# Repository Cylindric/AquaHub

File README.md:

# AquaHub

# Key Components

## Hardware

The electronic designs are all made using [KiCad](http://kicad-pcb.org).

The actual KiCad project files are [here](Hardware/AquaHub/).

Rendered output (schematic and board PDFs, gerbers and bom) are [here](Hardware/Output/). (Not always up-to-date with the schematics and boards, so use with caution)

### License

All hardware designs are licensed under the [CERN Open Hardware Licence v1.2](https://www.ohwr.org/licenses/cern-ohl/license_versions/v1.2).

Myriam Ayass, legal adviser of the Knowledge and Technology Transfer Group at CERN and author of the CERN OHL:

> In the spirit of knowledge sharing and dissemination, the CERN Open Hardware Licence (CERN OHL) governs the use, copying, modification and distribution of hardware design documentation, and the manufacture and distribution of products.
> 
> The CERN–OHL is to hardware what the General Public Licence (GPL) is to software. It defines the conditions under which a licensee will be able to use or modify the licensed material. The concept of ‘open-source hardware’ or ‘open hardware’ is not yet as well known or widespread as the free software or open-source software concept. However, it shares the same principles: anyone should be able to see the source (the design documentation in case of hardware), study it, modify it and share it.
> 
> In addition, if modifications are made and distributed, it must be under the same licence conditions – this is the ‘persistent’ nature of the licence, which ensures that the whole community will continue benefiting from improvements, in the sense that everyone will in turn be able to make modifications to these improvements.

### Rev 1
- [x] ESP32 module for control and wireless access (Espressif ESP32-WROOM-32D)
- [x] Current Sensing for consumption reporting and equipment failure detection (Melexis MLX91210KDC)
- [x] RTC for power-loss schedule persistence (Maxim DS1307Z)
- [x] Temperature monitoring (DS18B20)
- [x] Audible alarm
- [x] Six switchable mains-level outputs (Fujitsu FTR-F1A)
- [x] Direct mains-powered (Recom RAC04-12SGB)

### Rev 2
- [ ] PCB: selectable low-level power select, for testing from a 12V supply instead of 240V
- [x] PCB: additional sensor for ambient temperature (on-board or external?)
- [ ] PCB: additional input for flow-rate sensor
- [ ] PCB: additional input for pH sensor (might not be feasible without a permanent-immersion sensor?)
- [ ] PCB: LED power indication for ESP
- [x] PCB: Reset button for ESP
- [x] PCB: Test points for probe hooks
- [x] PCB: Change buttons to off-board panel buttons
- [ ] ENCLOSURE: Add a 6-pin socket for programming
- [ ] ENCLOSURE: Switched & fused power inlet receptacle
- [ ] ENCLOSURE: Non-PCB panel buttons - more choice, better buttons
- [ ] ENCLOSURE: Power LED

## Software

### License

All software (firmware) are Copyright 2018 Mark Hanford and licensed under the [Apache License, Version 2.0](http://www.apache.org/licenses/LICENSE-2.0) (the "License");

> You may not use this file except in compliance with the License. You may obtain a copy of the License at
>
> http://www.apache.org/licenses/LICENSE-2.0
>
> Unless required by applicable law or agreed to in writing, software distributed under the License is distributed on an "AS IS" BASIS, WITHOUT WARRANTIES OR CONDITIONS OF ANY KIND, either express or implied.
> See the License for the specific language governing permissions and limitations under the License.

### Rev 1
- [ ] Over-the-air firmware updates
- [ ] Web UI
- [ ] Task Scheduler
- [ ] Temperature-based control
- [ ] Temperature alarm
- [ ] Pump-fail alarm
- [ ] WiFi config

# Hardware Build

A Mouser project with some of the components listed in detail is available here: [AquaHub At Mouser](https://www.mouser.com/ProjectManager/ProjectDetail.aspx?AccessID=329311b4a5). Not always updated with the current BOM from the schematic, and parts change so may be unavailable. CHECK THE SCHEMATIC.

## Datasheets

* [Espressif ESP32 WROOM 32D](https://www.espressif.com/sites/default/files/documentation/esp32-wroom-32d_esp32-wroom-32u_datasheet_en.pdf)
* [Recom 5v Regulator](https://www.recom-power.com/pdf/Innoline/R-78Exx-0.5.pdf)
* [Diodes 3.3V Regulator](http://www.diodes.com/datasheets/AP1117.pdf)
* [2SC1815 Transistor](https://media.digikey.com/pdf/Data%20Sheets/Toshiba%20PDFs/2SC1815.pdf)
* [Maxim I²C RTC](https://datasheets.maximintegrated.com/en/ds/DS1307.pdf)
* [TI I²C IO Expander](http://www.ti.com/lit/ds/symlink/tca9534.pdf)
* [TI I²C LED Driver](http://www.ti.com/lit/ds/symlink/tpic2810.pdf)

## References

* DS18B20 temperature - [ESP32 With Multiple DS18B20 Sensors](https://randomnerdtutorials.com/esp32-with-multiple-ds18b20-temperature-sensors/)

# Attribution

* Fish icon is from [iconsDB](https://www.iconsdb.com/custom-color/fish-3-icon.html); Creative Commons Attribution-NoDerivs 3.0.

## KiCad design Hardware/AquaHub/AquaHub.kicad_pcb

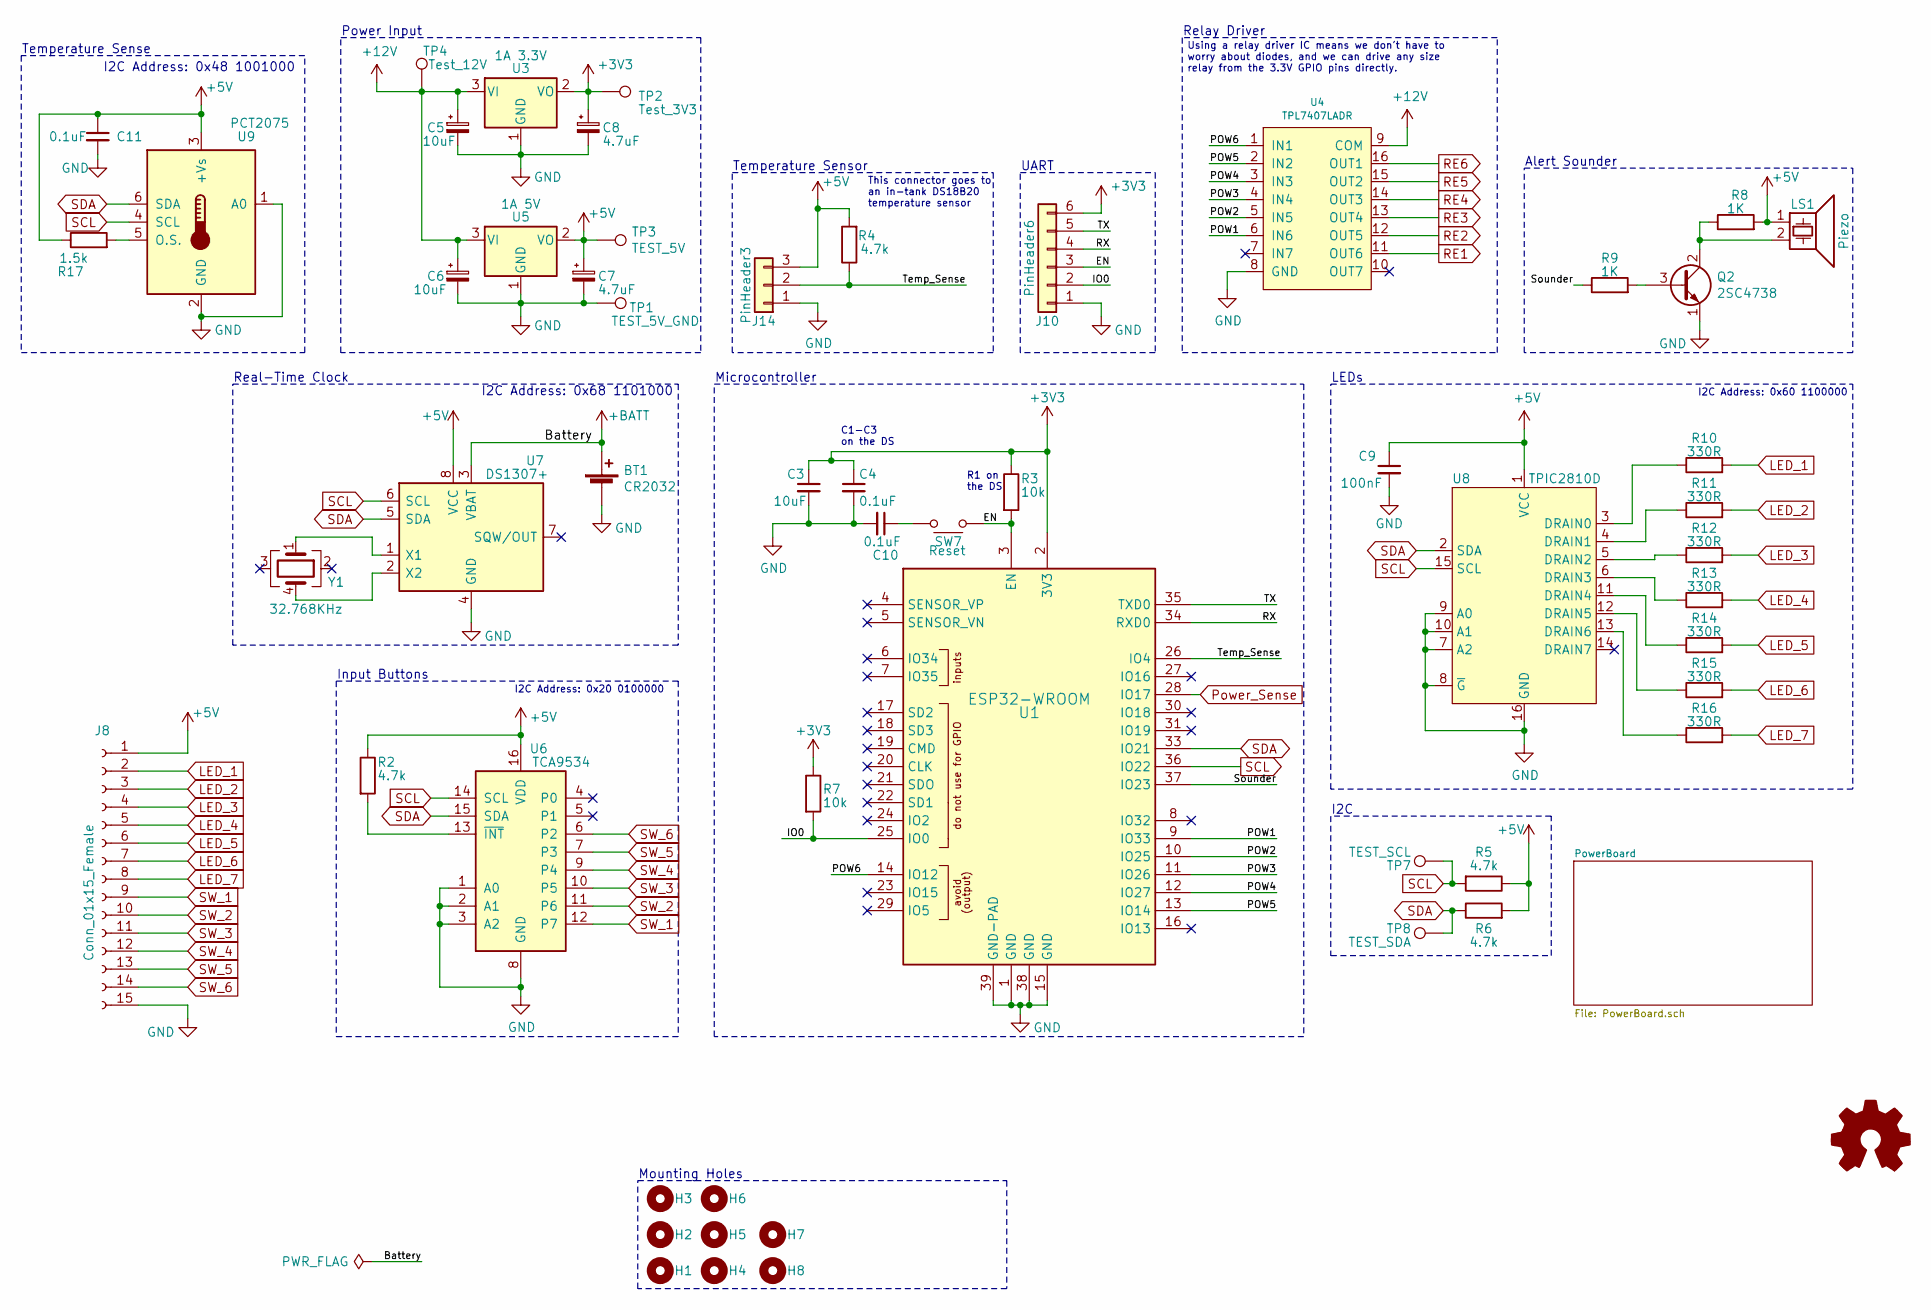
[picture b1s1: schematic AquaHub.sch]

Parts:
BT1: CR2032; BatteryHolder_Multicomp_BC-2001_1x2032; Mouser 534-1058
C3: 10uF; C_0805_2012Metric_Pad1.15x1.40mm_HandSolder; Mouser TAJB106K006SNJ
C4, C10, C11: 0.1uF; C_0805_2012Metric_Pad1.15x1.40mm_HandSolder; Mouser TAJB106K006SNJ
C5, C6: 10uF; CP_Elec_6.3x5.4_Nichicon; Farnell CA07886
C7, C8: 4.7uF; CP_Elec_5x5.4; Mouser UWX1H4R7MCL1GB
C9: 100nF; C_0603_1608Metric_Pad1.05x0.95mm_HandSolder; Farnell CA07658
H1, H2, H3, H4, H5, H6, H7, H8: MountingHole; MountingHole_3.2mm_M3
J8: Conn_01x15_Female; PinHeader_2x08_P2.00mm_Vertical; Mouser 798-DF51A-16DP-2DSA
J10: PinHeader6; PinHeader_1x06_P2.54mm_Vertical; Mouser 710-61300611121
J14: PinHeader3; PinHeader_1x03_P2.54mm_Vertical; Mouser 710-61300311121
LS1: Piezo; Buzzer_TDK_PS1240P02BT_D12.2mm_H6.5mm; Mouser PS1240P02BT
Q2: 2SC4738; SOT-416; Farnell SC06581
R2, R4, R5, R6: 4.7k; R_0603_1608Metric_Pad1.05x0.95mm_HandSolder; Mouser 603-RC0603FR-074K7L
R3, R7: 10k; R_0603_1608Metric_Pad1.05x0.95mm_HandSolder; Mouser 603-RC0603FR-0710KL
R8, R9: 1K; R_0603_1608Metric_Pad1.05x0.95mm_HandSolder; Farnell RE07090
R10, R11, R12, R13, R14, R15, R16: 330R; R_0603_1608Metric_Pad1.05x0.95mm_HandSolder; Farnell RE07105
R17: 1.5k; R_0603_1608Metric_Pad1.05x0.95mm_HandSolder; Mouser 603-RC0603FR-101K5L
SW7: Reset; SW_SPST_PTS645; Mouser 611-PTS645SM43SMTR92
TP1: TEST_5V_GND; TestPoint_Loop_D2.50mm_Drill1.0mm
TP2: Test_3V3; TestPoint_Loop_D2.50mm_Drill1.0mm
TP3: TEST_5V; TestPoint_Loop_D2.50mm_Drill1.0mm
TP4: Test_12V; TestPoint_Loop_D2.50mm_Drill1.0mm
TP7: TEST_SCL; TestPoint_Loop_D2.50mm_Drill1.0mm
TP8: TEST_SDA; TestPoint_Loop_D2.50mm_Drill1.0mm
U1: ESP32-WROOM; Espressif_ESP32_WROOM_32_SMT; Mouser ESP32-WROOM-32D
U3: 1A 3.3V; TO-252-3_TabPin2; Mouser NCP1117DT33G
U4: TPL7407LADR; SOIC-16_3.9x9.9mm_P1.27mm; Mouser 595-TPL7407LADR
U5: 1A 5V; TO-252-3_TabPin2; Mouser NCP1117DT50G
U6: TCA9534; SOIC-16W_7.5x10.3mm_P1.27mm; Mouser TCA9534DWR
U7: DS1307+; SOIC-8_3.9x4.9mm_P1.27mm; Mouser 700-DS1307ZT&R
U8: TPIC2810D; SOIC-16_3.9x9.9mm_P1.27mm; Mouser 595-TPIC2810DR
U9: PCT2075; TSOP-6_1.65x3.05mm_P0.95mm; Mouser 771-PCT2075GVX
Y1: 32.768KHz; Crystal_SMD_SeikoEpson_MC146-4Pin_6.7x1.5mm_HandSoldering; Mouser 732-MC146-32.7KAA0R

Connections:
+3V3: C3.1, C4.1, C8.1, J10.6, R3.1, R7.1, TP2.1, U1.2 (3V3), U3.2 (VO)
+5V: C7.1, C9.1, C11.1, J8.1, J14.3, LS1.1, R2.1, R4.2, R5.1, R6.2, R8.2, R17.1, TP3.1, U5.2 (VO), U6.16 (VDD), U7.8 (VCC), U8.1 (VCC), U9.3 (+Vs); also elsewhere on the board
+12V: C5.1, C6.1, TP4.1, U3.3 (VI), U4.9 (COM), U5.3 (VI); also elsewhere on the board
+BATT: BT1.1 (+), U7.3 (VBAT)
/EN: J10.3, R3.2, SW7.1 (A), SW7.3 (A), U1.3 (EN)
/IO0: J10.2, R7.2, U1.25 (IO0)
/POW1: U1.9 (IO33), U4.6 (IN6)
/POW2: U1.10 (IO25), U4.5 (IN5)
/POW3: U1.11 (IO26), U4.4 (IN4)
/POW4: U1.12 (IO27), U4.3 (IN3)
/POW5: U1.13 (IO14), U4.2 (IN2)
/POW6: U1.14 (IO12), U4.1 (IN1)
/RX: J10.4, U1.34 (RXD0)
/Sounder: R9.1, U1.37 (IO23)
/TX: J10.5, U1.35 (TXD0)
/Temp_Sense: J14.2, R4.1, U1.26 (IO4)
GND: BT1.2 (-), C3.2, C4.2, C5.2, C6.2, C7.2, C8.2, C9.2, C10.2, C11.2, J8.15, J10.1, J14.1, Q2.1 (E), TP1.1, U1.1 (GND), U1.15 (GND), U1.38 (GND), U1.39 (GND-PAD), U3.1 (GND), U4.8 (GND), U5.1 (GND), U6.1 (A0), U6.2 (A1), U6.3 (A2), U6.8 (GND), U7.4 (GND), U8.7 (A2), U8.8 (~G), U8.9 (A0), U8.10 (A1), U8.16 (GND), U9.1 (A0), U9.2 (GND); also elsewhere on the board
LED_1: J8.2, R10.2
LED_2: J8.3, R11.2
LED_3: J8.4, R12.2
LED_4: J8.5, R13.2
LED_5: J8.6, R14.2
LED_6: J8.7, R15.2
LED_7: J8.8, R16.2
unnamed: C10.1, SW7.2 (B), SW7.4 (B)
unnamed: LS1.2, Q2.2 (C), R8.1
unnamed: Q2.3 (B), R9.2
unnamed: R2.2, U6.13 (~INT~)
unnamed: R10.1, U8.3 (DRAIN0)
unnamed: R11.1, U8.4 (DRAIN1)
unnamed: R12.1, U8.5 (DRAIN2)
unnamed: R13.1, U8.6 (DRAIN3)
unnamed: R14.1, U8.11 (DRAIN4)
unnamed: R15.1, U8.12 (DRAIN5)
unnamed: R16.1, U8.13 (DRAIN6)
unnamed: R17.2, U9.5 (O.S.)
unnamed: U7.1 (X1), Y1.1
unnamed: U7.2 (X2), Y1.4
Power_Sense: U1.28 (IO17); also elsewhere on the board
RE1: U4.11 (OUT6); also elsewhere on the board
RE2: U4.12 (OUT5); also elsewhere on the board
RE3: U4.13 (OUT4); also elsewhere on the board
RE4: U4.14 (OUT3); also elsewhere on the board
RE5: U4.15 (OUT2); also elsewhere on the board
RE6: U4.16 (OUT1); also elsewhere on the board
SCL: R5.2, TP7.1, U1.36 (IO22), U6.14 (SCL), U7.6 (SCL), U8.15 (SCL), U9.4 (SCL)
SDA: R6.1, TP8.1, U1.33 (IO21), U6.15 (SDA), U7.5 (SDA), U8.2 (SDA), U9.6 (SDA)
SW_1: J8.9, U6.12 (P7)
SW_2: J8.10, U6.11 (P6)
SW_3: J8.11, U6.10 (P5)
SW_4: J8.12, U6.9 (P4)
SW_5: J8.13, U6.7 (P3)
SW_6: J8.14, U6.6 (P2)

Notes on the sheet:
UART
Power Input
Relay Driver
Temperature Sensor
This connector goes to an in-tank DS18B20 temperature sensor
Using a relay driver IC means we don't have to worry about diodes, and we can drive any size relay from the 3.3V GPIO pins directly.
Microcontroller
Alert Sounder
Real-Time Clock
I2C Address: 0x68 1101000
Mounting Holes
Input Buttons
LEDs
I2C Address: 0x60 1100000
I2C Address: 0x20 0100000
I2C
C1-C3 on the DS
R1 on the DS
I2C Address: 0x48 1001000
Temperature Sense

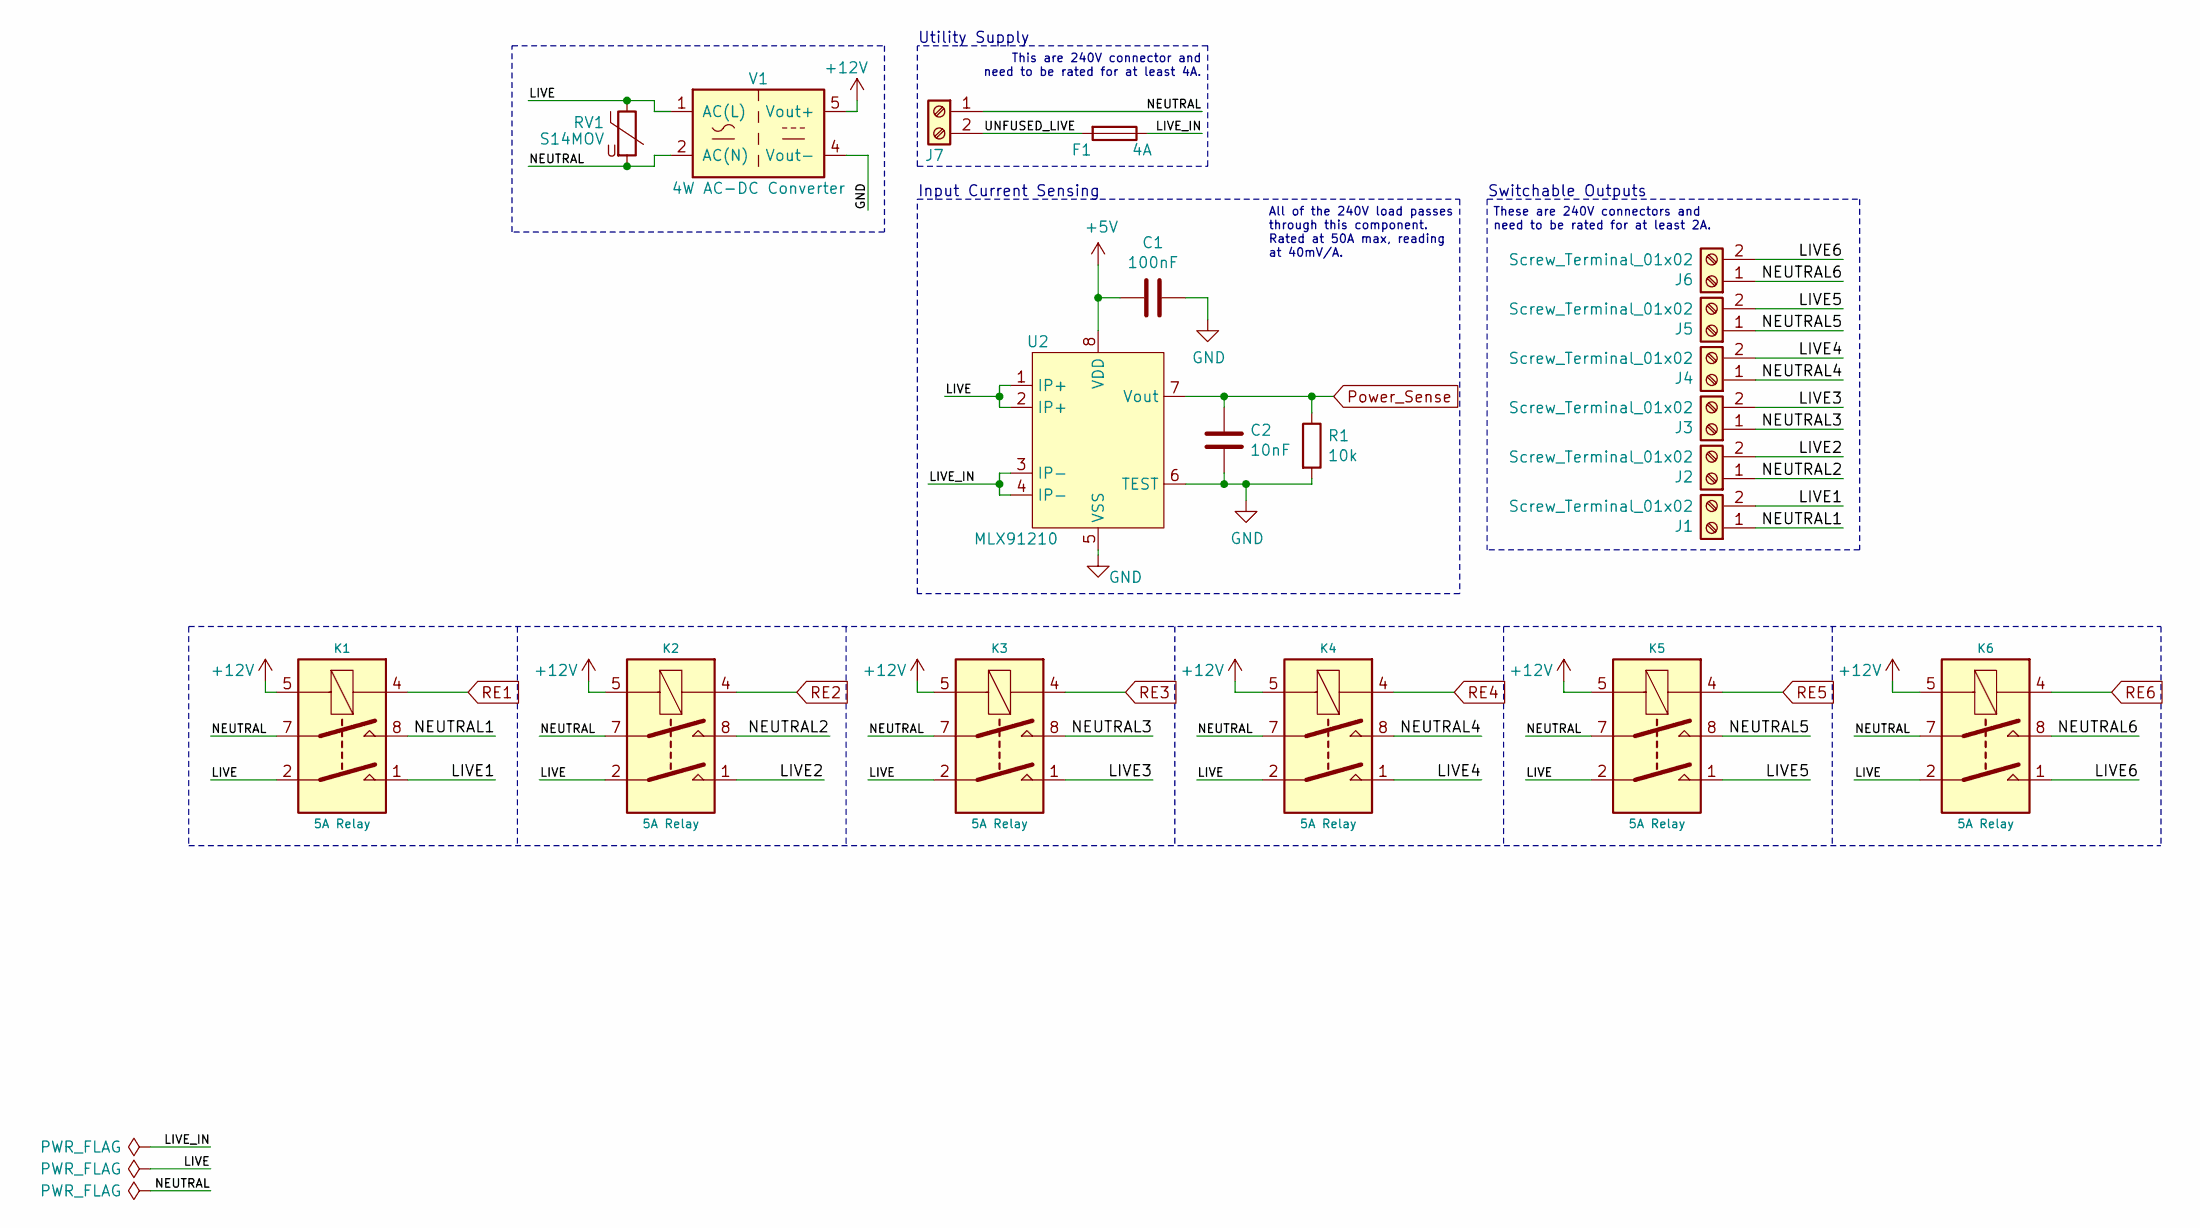
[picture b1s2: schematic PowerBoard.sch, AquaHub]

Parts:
C1: 100nF; C_0603_1608Metric_Pad1.05x0.95mm_HandSolder; Farnell CA07658
C2: 10nF; C_0603_1608Metric_Pad1.05x0.95mm_HandSolder; Mouser VJ0603A102GXAPW1BC
F1: 4A; Fuseholder_Glass_5mmx20mm; Mouser 534-3512
J1, J2, J3, J4, J5, J6, J7: Screw_Terminal_01x02; TerminalBlock_Phoenix_PT-1,5-2-5.0-H_1x02_P5.00mm_Horizontal; Mouser 1935161
K1, K2, K3, K4, K5, K6: 5A Relay; Relay_DPST_Fujitsu_FTR-F1A; Mouser FTR-F1AA012V
R1: 10k; R_0603_1608Metric_Pad1.05x0.95mm_HandSolder; Mouser 603-RC0603FR-0710KL
RV1: S14MOV; RV_Disc_D15.5mm_W6.1mm_P7.5mm; Mouser B72214P2251K101
U2: MLX91210; SOIC-8_3.9x4.9mm_P1.27mm; Mouser MLX91210KDC-CAS-102-SP
V1: 4W AC-DC Converter; Converter_ACDC_RECOM_RAC04-xxSGx_THT; Mouser RAC04-12SGB

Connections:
+5V: C1.2, U2.8 (VDD); also elsewhere on the board
+12V: K1.5, K2.5, K3.5, K4.5, K5.5, K6.5, V1.5 (Vout+); also elsewhere on the board
/PowerBoard/LIVE: K1.2, K2.2, K3.2, K4.2, K5.2, K6.2, RV1.1, U2.1 (IP+), U2.2 (IP+), V1.1 (AC(L))
/PowerBoard/LIVE1: J1.2, K1.1
/PowerBoard/LIVE2: J2.2, K2.1
/PowerBoard/LIVE3: J3.2, K3.1
/PowerBoard/LIVE4: J4.2, K4.1
/PowerBoard/LIVE5: J5.2, K5.1
/PowerBoard/LIVE6: J6.2, K6.1
/PowerBoard/LIVE_IN: F1.1, U2.3 (IP-), U2.4 (IP-)
/PowerBoard/NEUTRAL: J7.1, K1.7, K2.7, K3.7, K4.7, K5.7, K6.7, RV1.2, V1.2 (AC(N))
/PowerBoard/NEUTRAL1: J1.1, K1.8
/PowerBoard/NEUTRAL2: J2.1, K2.8
/PowerBoard/NEUTRAL3: J3.1, K3.8
/PowerBoard/NEUTRAL4: J4.1, K4.8
/PowerBoard/NEUTRAL5: J5.1, K5.8
/PowerBoard/NEUTRAL6: J6.1, K6.8
/PowerBoard/UNFUSED_LIVE: F1.2, J7.2
GND: C1.1, C2.2, R1.2, U2.5 (VSS), U2.6 (TEST), V1.4 (Vout-); also elsewhere on the board
Power_Sense: C2.1, R1.1, U2.7 (Vout); also elsewhere on the board
RE1: K1.4; also elsewhere on the board
RE2: K2.4; also elsewhere on the board
RE3: K3.4; also elsewhere on the board
RE4: K4.4; also elsewhere on the board
RE5: K5.4; also elsewhere on the board
RE6: K6.4; also elsewhere on the board

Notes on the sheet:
Switchable Outputs
These are 240V connectors and need to be rated for at least 2A.
Utility Supply
This are 240V connector and need to be rated for at least 4A.
Input Current Sensing
All of the 240V load passes through this component. Rated at 50A max, reading at 40mV/A.

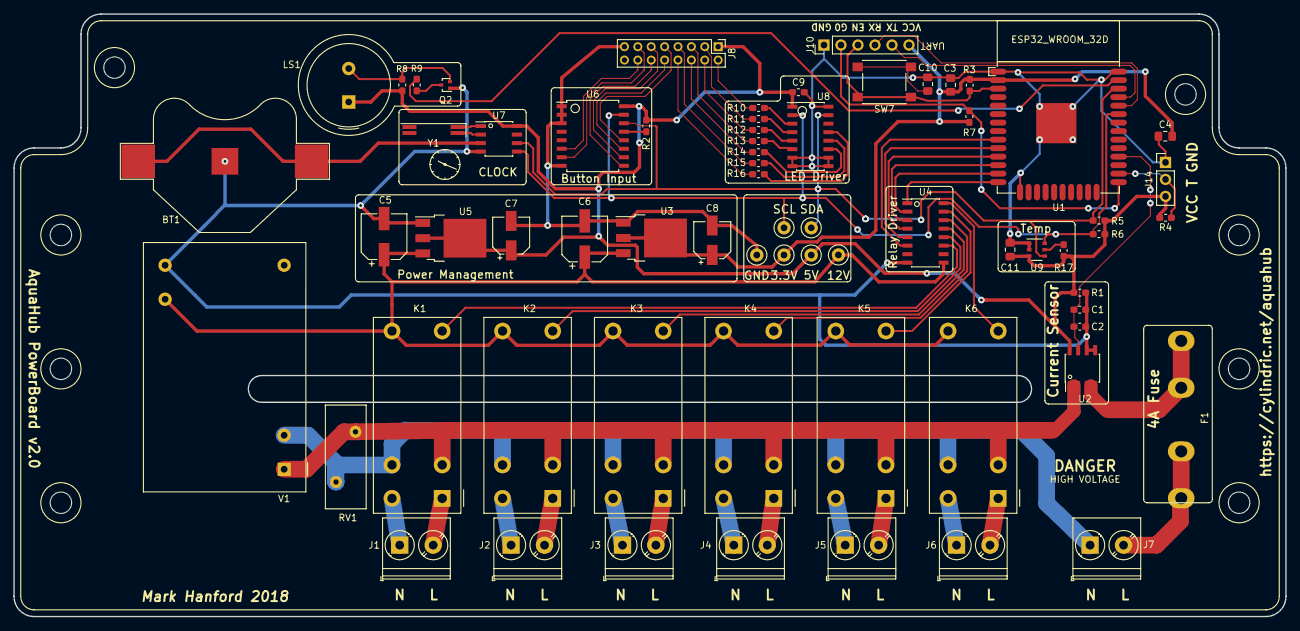
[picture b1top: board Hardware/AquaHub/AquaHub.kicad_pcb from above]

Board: 2 copper layers, 190.0 x 90.0 mm, 75 parts (0 on the bottom side), 69 nets.

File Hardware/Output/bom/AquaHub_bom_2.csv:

Component,Description,Part,References,Value,Footprint,Quantity Per PCB,Datasheet,Mouser,Vendor,Farnell,RS
1,b'',b'Battery_Cell-Device',b'BT1',b'CR2032',b'BatteryHolder_Multicomp_BC-2001_1x2032',b'1',b'~',b'534-1058',b'Mouser',b'',b''
2,b'',b'C_Small-Device',b'C4 C10 C11',b'0.1uF',b'C_0805_2012Metric_Pad1.15x1.40mm_HandSolder',b'3',b'~',b'TAJB106K006SNJ',b'Mouser',b'',b''
3,b'',b'C-Device',b'C1',b'100nF',b'C_0603_1608Metric_Pad1.05x0.95mm_HandSolder',b'1',b'~',b'710-885012206071',b'Mouser',b'CA07658',b''
4,"b'Unpolarized capacitor, small symbol'",b'C_Small',b'C9',b'100nF',b'C_0603_1608Metric_Pad1.05x0.95mm_HandSolder',b'1',b'~',b'710-885012206071',b'',b'CA07658',b''
5,b'',b'C-Device',b'C2',b'10nF',b'C_0603_1608Metric_Pad1.05x0.95mm_HandSolder',b'1',b'~',b'VJ0603A102GXAPW1BC',b'Mouser',b'',b''
6,b'',b'C_Small-Device',b'C3',b'10uF',b'C_0805_2012Metric_Pad1.15x1.40mm_HandSolder',b'1',b'~',b'TAJB106K006SNJ',b'Mouser',b'',b''
7,b'',b'CP_Small-Device',b'C5 C6',b'10uF',b'CP_Elec_6.3x5.4_Nichicon',b'2',b'~',b'UWX1H100MCL1GB',b'Mouser',b'CA07886',b''
8,b'',b'CP_Small-Device',b'C7 C8',b'4.7uF',b'CP_Elec_5x5.4',b'2',b'~',b'UWX1H4R7MCL1GB',b'Mouser',b'',b''
9,b'',b'Fuse-Device',b'F1',b'4A',b'Fuseholder_Glass_5mmx20mm',b'1',b'~',b'534-3512',b'Mouser',b'',b''
10,"b'Generic connector, single row, 01x15, script generated (kicad-library-utils/schlib/autogen/connector/)'",b'Conn_01x15_Female',b'J8',b'Conn_01x15_Female',b'PinHeader_2x08_P2.00mm_Vertical',b'1',b'https://www.mouser.co.uk/datasheet/2/185/DF51_catalog-1274968.pdf',b'798-DF51A-16DP-2DSA',b'',b'',b''
11,b'',b'Conn_01x03-Connector_Generic',b'J14',b'PinHeader3',b'PinHeader_1x03_P2.54mm_Vertical',b'1',b'~',b'710-61300311121',b'',b'',b''
12,b'',b'Conn_01x06-Connector_Generic',b'J10',b'PinHeader6',b'PinHeader_1x06_P2.54mm_Vertical',b'1',b'~',b'710-61300611121',b'',b'',b''
13,b'',b'Screw_Terminal_01x02-Connector',b'J1 J2 J3 J4 J5 J6 J7',b'Screw_Terminal_01x02',"b'TerminalBlock_Phoenix_PT-1,5-2-5.0-H_1x02_P5.00mm_Horizontal'",b'7',b'~',b'1935161',b'Mouser',b'',b''
14,b'',b'Fujitsu_FTR-F1A-Relay',b'K1 K2 K3 K4 K5 K6',b'5A Relay',b'Relay_DPST_Fujitsu_FTR-F1A',b'6',b'',b'FTR-F1AA012V',b'Mouser',b'',b''
15,b'Crystal speaker/transducer',b'Speaker_Crystal',b'LS1',b'Piezo',b'Buzzer_TDK_PS1240P02BT_D12.2mm_H6.5mm',b'1',b'~',b'PS1240P02BT',b'Mouser',b'',b''
16,b'',b'2SC1815-Transistor_BJT',b'Q2',b'2SC4738',b'SOT-416',b'1',b'http://www.semicon.toshiba.co.jp/info/lookup.jsp?pid=2SC4738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,b'757-2SC4738-YLF',b'Mouser',b'SC06581',b''
17,b'Resistor',b'R',b'R17',b'1.5k',b'R_0603_1608Metric_Pad1.05x0.95mm_HandSolder',b'1',b'~',b'603-RC0603FR-101K5L',b'Mouser',b'',b''
18,b'',b'R-Device',b'R1 R3 R7',b'10k',b'R_0603_1608Metric_Pad1.05x0.95mm_HandSolder',b'3',b'~',b'603-RC0603FR-0710KL',b'Mouser',b'',b''
19,b'',b'R-Device',b'R8 R9',b'1K',b'R_0603_1608Metric_Pad1.05x0.95mm_HandSolder',b'2',b'~',b'603-RC0603FR-071KL',b'Mouser',b'RE07090',b''
20,b'',b'R-Device',b'R10 R11 R12 R13 R14 R15 R16',b'330R',b'R_0603_1608Metric_Pad1.05x0.95mm_HandSolder',b'7',b'~',b'603-RC0603FR-07330RL',b'Mouser',b'RE07105',b''
21,b'Resistor',b'R',b'R2 R4',b'4.7k',b'R_0603_1608Metric_Pad1.05x0.95mm_HandSolder',b'2',b'~',b'603-RC0603FR-074K7L',b'Mouser',b'',b''
22,b'',b'R-Device',b'R5 R6',b'4.7k',b'R_0603_1608Metric_Pad1.05x0.95mm_HandSolder',b'2',b'~',b'603-RC0603FR-074K7L',b'Mouser',b'',b''
23,b'',b'Varistor-Device',b'RV1',b'S14MOV',b'RV_Disc_D15.5mm_W6.1mm_P7.5mm',b'1',b'~',b'B72214P2251K101',b'Mouser',b'',b''
24,b'',b'SW_CK_D6R_SPST-Switch',b'SW7',b'Reset',b'SW_SPST_PTS645',b'1',b'',b'611-PTS645SM43SMTR92',b'Mouser',b'',b''
25,b'',b'NCP1117-3.3_TO252-Regulator_Linear',b'U3',b'1A 3.3V',b'TO-252-3_TabPin2',b'1',b'http://www.diodes.com/datasheets/AP1117.pdf',b'NCP1117DT33G',b'Mouser',b'',b''
26,b'',b'NCP1117-5.0_TO252-Regulator_Linear',b'U5',b'1A 5V',b'TO-252-3_TabPin2',b'1',b'https://www.recom-power.com/pdf/Innoline/R-78Exx-0.5.pdf',b'NCP1117DT50G',b'Mouser',b'',b''
27,b'',b'DS1307+-Timer_RTC',b'U7',b'DS1307+',b'SOIC-8_3.9x4.9mm_P1.27mm',b'1',b'https://datasheets.maximintegrated.com/en/ds/DS1307.pdf',b'700-DS1307ZT&R',b'',b'',b''
28,b'',b'ESP32-WROOM-32-MCU_Espressif',b'U1',b'ESP32-WROOM',b'Espressif_ESP32_WROOM_32_SMT',b'1',b'',b'ESP32-WROOM-32D',b'Mouser',b'',b''
29,b'',b'MLX91210-AquaParts',b'U2',b'MLX91210',b'SOIC-8_3.9x4.9mm_P1.27mm',b'1',b'http://www.allegromicro.com/~/media/Files/Datasheets/ACS723-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,b'MLX91210KDC-CAS-102-SP',b'Mouser',b'',b''
30,"b' Digital Temperature Sensor & Thermal Watchdog, SOIC-8 and VSSOP-8'",b'PCT2075-TSOP6',b'U9',b'PCT2075',b'TSOP-6_1.65x3.05mm_P0.95mm',b'1',b'https://www.mouser.co.uk/datasheet/2/302/PCT2075-1127732.pdf',b'771-PCT2075GVX',b'',b'',b''
31,b'',b'TCA9534-Interface_Expansion',b'U6',b'TCA9534',b'SOIC-16W_7.5x10.3mm_P1.27mm',b'1',b'http://www.ti.com/lit/ds/symlink/tca9534.pdf',b'TCA9534DWR',b'Mouser',b'',b''
32,b'8-bit LED driver with I2C interface',b'TPIC2810D',b'U8',b'TPIC2810D',b'SOIC-16_3.9x9.9mm_P1.27mm',b'1',b'http://www.ti.com/lit/ds/symlink/tpic2810.pdf',b'595-TPIC2810DR',b'',b'',b'660-7981'
33,b'',b'TPL7407LA-AquaParts',b'U4',b'TPL7407LADR',b'SOIC-16_3.9x9.9mm_P1.27mm',b'1',b'http://www.ti.com/lit/ds/symlink/tpl7407la.pdf',b'595-TPL7407LADR',b'Mouser',b'',b''
34,b'',b'RAC04-xxGA-Converter_ACDC',b'V1',b'4W AC-DC Converter',b'Converter_ACDC_RECOM_RAC04-xxSGx_THT',b'1',b'',b'RAC04-12SGB',b'',b'',b''
35,"b'Four pin crystal, GND on pins 2 and 3'",b'Crystal_GND23',b'Y1',b'32.768KHz',b'Crystal_SMD_SeikoEpson_MC146-4Pin_6.7x1.5mm_HandSoldering',b'1',b'~',b'732-MC146-32.7KAA0R',b'',b'',b''





Component Groups:,35
Component Count:,61
Fitted Components:,61
Number of PCBs:,1
Total components:,61
Schematic Version:,2
Schematic Date:,2018-08-28
BoM Date:,b'17/11/2018 01:01:26'
Schematic Source:,b'D:\\AquaHub\\Hardware\\AquaHub\\AquaHub.sch'
KiCad Version:,b'Eeschema (6.0.0-rc1-dev-904-g29e0e6921)'

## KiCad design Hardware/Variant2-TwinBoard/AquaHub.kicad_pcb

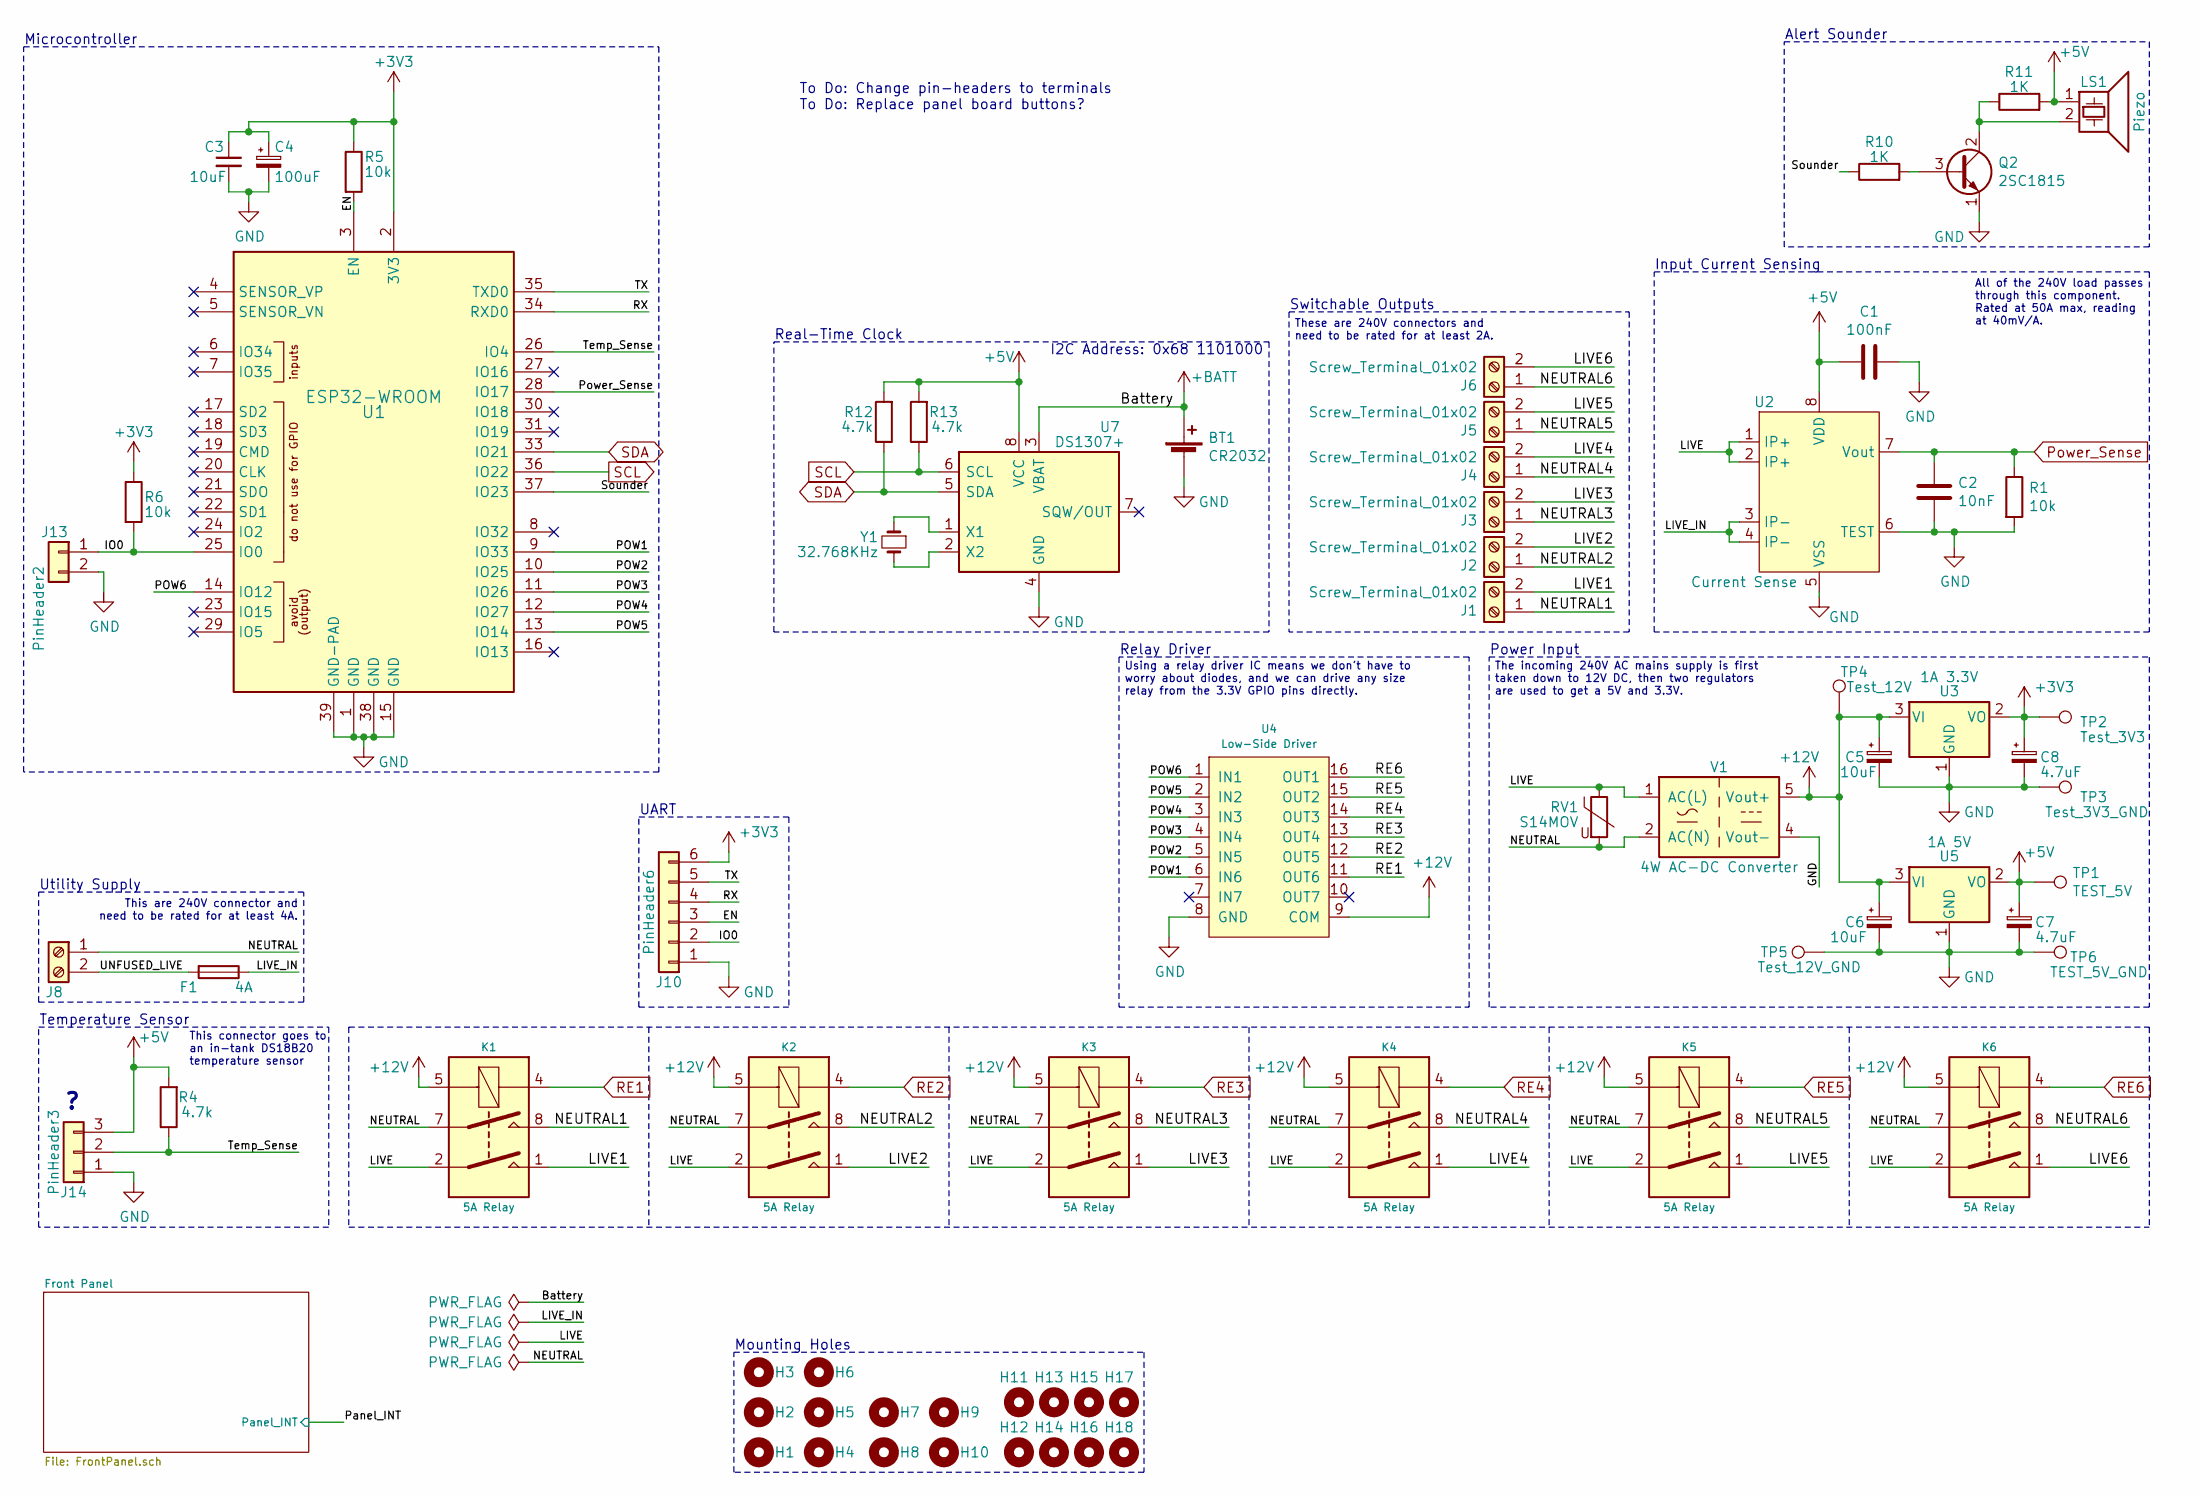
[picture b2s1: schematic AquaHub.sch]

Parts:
BT1: CR2032; Multicomp-BC-2001
C1: 100nF; C_0603_1608Metric_Pad1.05x0.95mm_HandSolder
C2: 10nF; C_0603_1608Metric_Pad1.05x0.95mm_HandSolder
C3: 10uF; C_0805_2012Metric_Pad1.15x1.40mm_HandSolder
C4: 100uF; CP_EIA-3528-21_Kemet-B_Pad1.50x2.35mm_HandSolder
C5, C6: 10uF; CP_Elec_6.3x5.4_Nichicon
C7, C8: 4.7uF; CP_Elec_5x5.4
F1: 4A; Fuseholder_Blade_Mini_Keystone_3568
H1, H2, H3, H4, H5, H6, H7, H8, H9, H10: MountingHole; MountingHole_3.2mm_M3
H11, H12, H13, H14, H15, H16, H17, H18: MountingHole; Breakaway 1mm
J1, J2, J3, J4, J5, J6, J8: Screw_Terminal_01x02; TerminalBlock_Phoenix_PT-1,5-2-5.0-H_1x02_P5.00mm_Horizontal
J10: PinHeader6; PinHeader_1x06_P2.54mm_Vertical
J13: PinHeader2; PinHeader_1x02_P2.54mm_Vertical
J14: PinHeader3; PinHeader_1x03_P2.54mm_Vertical
K1, K2, K3, K4, K5, K6: 5A Relay; Relay_DPST_Fujitsu_FTR-F1A
LS1: Piezo; Buzzer_TDK_PS1240P02BT_D12.2mm_H6.5mm
Q2: 2SC1815; SOT-23
R1, R5, R6: 10k; R_0603_1608Metric_Pad1.05x0.95mm_HandSolder
R4, R12, R13: 4.7k; R_0603_1608Metric_Pad1.05x0.95mm_HandSolder
R10, R11: 1K; R_0603_1608Metric_Pad1.05x0.95mm_HandSolder
RV1: S14MOV; RV_Disc_D15.5mm_W6.1mm_P7.5mm
TP1: TEST_5V; TestPoint_Keystone_5010-5014_Multipurpose
TP2: Test_3V3; TestPoint_Keystone_5010-5014_Multipurpose
TP3: Test_3V3_GND; TestPoint_Keystone_5010-5014_Multipurpose
TP4: Test_12V; TestPoint_Keystone_5010-5014_Multipurpose
TP5: Test_12V_GND; TestPoint_Keystone_5010-5014_Multipurpose
TP6: TEST_5V_GND; TestPoint_Keystone_5010-5014_Multipurpose
U1: ESP32-WROOM; Espressif_ESP32_WROOM_32_SMT
U2: Current Sense; SOIC-8_3.9x4.9mm_P1.27mm
U3: 1A 3.3V; TO-252-3_TabPin2
U4: Low-Side Driver; SOIC-16_3.9x9.9mm_P1.27mm
U5: 1A 5V; TO-252-3_TabPin2
U7: DS1307+; SOIC-8_3.9x4.9mm_P1.27mm
V1: 4W AC-DC Converter; Converter_ACDC_RECOM_RAC04-xxSGx_THT
Y1: 32.768KHz; Crystal_C26-LF_D2.1mm_L6.5mm_Horizontal

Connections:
+3V3: C3.1, C4.1, C8.1, J10.6, R5.1, R6.1, TP2.1, U1.2 (3V3), U3.2 (VO)
+5V: C1.2, C7.1, J14.3, LS1.1, R4.2, R11.2, R12.2, R13.2, TP1.1, U2.8 (VDD), U5.2 (VO), U7.8 (VCC); also elsewhere on the board
+12V: C5.1, C6.1, K1.5, K2.5, K3.5, K4.5, K5.5, K6.5, TP4.1, U3.3 (VI), U4.9 (COM), U5.3 (VI), V1.5 (Vout+); also elsewhere on the board
+BATT: BT1.1 (+), U7.3 (VBAT)
/EN: J10.3, R5.2, U1.3 (EN)
/IO0: J10.2, J13.1, R6.2, U1.25 (IO0)
/LIVE: K1.2, K2.2, K3.2, K4.2, K5.2, K6.2, RV1.1, U2.1 (IP+), U2.2 (IP+), V1.1 (AC(L))
/LIVE1: J1.2, K1.1
/LIVE2: J2.2, K2.1
/LIVE3: J3.2, K3.1
/LIVE4: J4.2, K4.1
/LIVE5: J5.2, K5.1
/LIVE6: J6.2, K6.1
/LIVE_IN: F1.1, U2.3 (IP-), U2.4 (IP-)
/NEUTRAL: J8.1, K1.7, K2.7, K3.7, K4.7, K5.7, K6.7, RV1.2, V1.2 (AC(N))
/NEUTRAL1: J1.1, K1.8
/NEUTRAL2: J2.1, K2.8
/NEUTRAL3: J3.1, K3.8
/NEUTRAL4: J4.1, K4.8
/NEUTRAL5: J5.1, K5.8
/NEUTRAL6: J6.1, K6.8
/POW1: U1.9 (IO33), U4.6 (IN6)
/POW2: U1.10 (IO25), U4.5 (IN5)
/POW3: U1.11 (IO26), U4.4 (IN4)
/POW4: U1.12 (IO27), U4.3 (IN3)
/POW5: U1.13 (IO14), U4.2 (IN2)
/POW6: U1.14 (IO12), U4.1 (IN1)
/RX: J10.4, U1.34 (RXD0)
/Sounder: R10.1, U1.37 (IO23)
/TX: J10.5, U1.35 (TXD0)
/Temp_Sense: J14.2, R4.1, U1.26 (IO4)
/UNFUSED_LIVE: F1.2, J8.2
GND: BT1.2 (-), C1.1, C2.2, C3.2, C4.2, C5.2, C6.2, C7.2, C8.2, J10.1, J13.2, J14.1, Q2.1 (E), R1.2, TP3.1, TP5.1, TP6.1, U1.1 (GND), U1.15 (GND), U1.38 (GND), U1.39 (GND-PAD), U2.5 (VSS), U2.6 (TEST), U3.1 (GND), U4.8 (GND), U5.1 (GND), U7.4 (GND), V1.4 (Vout-); also elsewhere on the board
unnamed: LS1.2, Q2.2 (C), R11.1
unnamed: Q2.3 (B), R10.2
unnamed: U7.1 (X1), Y1.1
unnamed: U7.2 (X2), Y1.2
Power_Sense: C2.1, R1.1, U1.28 (IO17), U2.7 (Vout); also elsewhere on the board
RE1: K1.4, U4.11 (OUT6); also elsewhere on the board
RE2: K2.4, U4.12 (OUT5); also elsewhere on the board
RE3: K3.4, U4.13 (OUT4); also elsewhere on the board
RE4: K4.4, U4.14 (OUT3); also elsewhere on the board
RE5: K5.4, U4.15 (OUT2); also elsewhere on the board
RE6: K6.4, U4.16 (OUT1); also elsewhere on the board
SCL: R13.1, U1.36 (IO22), U7.6 (SCL); also elsewhere on the board
SDA: R12.1, U1.33 (IO21), U7.5 (SDA); also elsewhere on the board

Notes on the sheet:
Input Current Sensing
UART
Power Input
Relay Driver
To Do: Change pin-headers to terminals To Do: Replace panel board buttons?
Switchable Outputs
Temperature Sensor
This connector goes to an in-tank DS18B20 temperature sensor
These are 240V connectors and need to be rated for at least 2A.
Utility Supply
This are 240V connector and need to be rated for at least 4A.
Using a relay driver IC means we don't have to worry about diodes, and we can drive any size relay from the 3.3V GPIO pins directly.
The incoming 240V AC mains supply is first taken down to 12V DC, then two regulators are used to get a 5V and 3.3V.
All of the 240V load passes through this component. Rated at 50A max, reading at 40mV/A.
Microcontroller
Alert Sounder
Real-Time Clock
I2C Address: 0x68 1101000
Mounting Holes
